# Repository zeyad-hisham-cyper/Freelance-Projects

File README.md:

# Freelance Projects

A portfolio of embedded systems, PCB design and IoT projects delivered for freelance clients and events, from schematic and PCB layout through firmware to companion mobile apps.

**Core skills:** ESP32 · Arduino / PlatformIO (C++) · KiCad 9 PCB design · sensor integration (IMU, IR temperature, load cells, PPG) · BLE · ESP-NOW · nRF24L01+ · Flutter · Li-Po power design

---

## Projects

| | Project | What it is | Hardware | Firmware / Software |
|---|---|---|:---:|:---:|
|  | **[Smart Posture Corrector](Smart-Posture-Corrector/)** | Two-board wearable with two IMUs that vibrates when you slouch and streams posture data to a Flutter app over BLE. | ✅ KiCad (2 boards) | ✅ ESP32 firmware + Flutter app |
|  | **[Digital Weighing Scale](Digital-Weighing-Scale/)** | Load-cell weighing indicator built in stages: research, ESP-NOW prototype, then a modular "one firmware, many scales" controller with a wireless remote display. | Research + BOM | ✅ Arduino / ESP32 firmware, Nextion HMI |
|  | **[Cow Health Monitor](Cow-Health-Monitor/)** | ESP32 carrier board plus two remote sensor boards for a livestock collar: body temperature, heart rate / SpO₂, motion and GPS. | ✅ KiCad (1- and 2-layer variants) | — |
|  | **[Smart Emergency Dispatch Sensor](Smart-Emergency-Dispatch-Sensor/)** | ESP32 board with an IR thermometer, a 6-axis IMU, a GPS header and a buzzer/LED alarm for heat, fire or impact events. | ✅ KiCad, 2-layer THT | — |
|  | **[Telecom Village SIM Adapter Badge](TelecomVillage-SIM-Adapter-Badge/)** | Credit-card-sized conference badge that doubles as a 2FF / 3FF / 4FF smart-card adapter, with ISO 7816 contacts broken out to test pads. | ✅ KiCad, SMT-assembly ready | — |

Each project folder has its own README with an overview, block diagram, BOM, pin mapping, PCB specifications, build instructions and a render gallery.

---

## Repository layout

```
Freelance-Projects/
├── Smart-Posture-Corrector/           # ESP32 firmware (PlatformIO) + Flutter app + KiCad PCBs
├── Digital-Weighing-Scale/            # Load-cell firmware (MVP + v2), Nextion HMI, research figures
├── Cow-Health-Monitor/                # KiCad PCB set + vendor 3D models
├── Smart-Emergency-Dispatch-Sensor/   # KiCad PCB + Gerbers
├── TelecomVillage-SIM-Adapter-Badge/  # KiCad PCB, Gerbers, pick-and-place, badge artwork
└── kicad-shared-lib/                  # Symbols, footprints and 3D models shared by several boards
```

Every hardware project follows the same pattern:

- **KiCad source:** `*.kicad_pro`, `*.kicad_sch`, `*.kicad_pcb`
- **Fabrication outputs:** Gerber and drill files, plus a zip ready to upload to JLCPCB / PCBWay
- **`docs/`:** 3D renders, PCB layout, schematic (SVG + PDF)

## Opening the KiCad projects

1. Install **KiCad 9.x**.
2. Clone the whole repository. Some boards load 3D models from `kicad-shared-lib/` or a sibling project through `${KIPRJMOD}`-relative paths, so the folder structure must stay intact.
3. Open the `.kicad_pro` file in the project folder.

## Regenerating the figures

The renders in each `docs/images/` folder were produced with `kicad-cli`:

```bash
kicad-cli pcb render --quality high --width 1600 --height 1000 --rotate " -45,0,35" -o docs/images/pcb_3d_iso.png board.kicad_pcb
kicad-cli pcb render --side top    --quality high -o docs/images/pcb_3d_top.png    board.kicad_pcb
kicad-cli pcb render --side bottom --quality high -o docs/images/pcb_3d_bottom.png board.kicad_pcb
kicad-cli pcb export svg --layers "F.Cu,B.Cu,Edge.Cuts,F.Silkscreen" --mode-single --page-size-mode 2 --exclude-drawing-sheet -o docs/images/pcb_layout.svg board.kicad_pcb
kicad-cli sch export svg -o docs/images/schematic board.kicad_sch
kicad-cli sch export pdf -o docs/schematic.pdf board.kicad_sch
```

## Third-party content

- Vendor symbols, footprints and 3D models (SnapEDA, DFRobot, CUI, GCT and others) remain under their owners' licences.
- The 3D-printable load-cell frame in `Digital-Weighing-Scale/` is © indrekluuk ([Thingiverse 4602226](https://www.thingiverse.com/thing:4602226)), licensed CC BY-NC.
- Event and university logos on the silkscreens belong to their respective owners.

---

**Author:** [@zeyad-hisham-cyper](https://github.com/zeyad-hisham-cyper) — Embedded Systems & PCB Design

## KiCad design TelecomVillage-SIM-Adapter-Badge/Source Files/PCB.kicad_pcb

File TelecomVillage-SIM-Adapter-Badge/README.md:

# Telecom Village Badge — Smart Card 2FF / 3FF / 4FF Adapter

> A credit-card-style conference badge PCB for **Telecom Village** (*"Malware Edition"*). It is also a working tool: three SIM-card sockets (Mini, Micro and Nano SIM) share one bus, and the ISO 7816 smart-card contacts are broken out to large test pads for probing.

| Front artwork | Back artwork |
|---|---|
|  |  |

---

## Overview

The board is a 2-layer, 1.6 mm FR-4 PCB. It is about **108 × 54 mm** with rounded corners, so it has the look of an event badge. The silkscreen on the copper side is **Telecom Village** artwork: a hooded hacker figure with a cell tower and a satellite dish, *"MALWARE EDITION"*, and the names of well-known telecom attacks and malware (SIMjacker, A5/1 cracker, GTPStorm, LightBasin, Skylock, Hermit spyware, VoLTEr attack). The silkscreen text names the board **"SMART CARD 2FF / 3FF / 4FF ADAPTER V1"**. The back carries a sponsor logo.

The design has no active parts. It has no MCU, regulator or firmware. Electrically it is a **passive SIM / UICC breakout**:

- **J2** is a 2FF (Mini SIM) socket, **J3** a 3FF (Micro SIM) socket and **J1** a 4FF (Nano SIM) socket. All three are wired in parallel to the same ISO 7816 nets.
- Eight **3.5 × 2 mm SMD test pads** (J4–J11) expose VCC, RST, CLK, I/O, VPP, GND and two spare AUX lines. You can connect them to a logic analyser, a smart-card reader, an SDR/SIM-tracing setup or a microcontroller.

*Inferred use:* hands-on SIM/UICC workshops at the village, such as sniffing APDUs, attaching a reader to a card of any size, or adapting one form factor to another. The design files don't state this. It follows from the topology and the event theme.

## Key features

- **Three SIM form factors on one badge:** 2FF / 3FF / 4FF sockets from CUI Devices and GCT.
- **All ISO 7816 contacts broken out:** C1 VCC, C2 RST, C3 CLK, C5 GND, C6 VPP and C7 I/O go to large SMD pads that are easy to clip or probe.
- **Two extra AUX pads** (AUX1/AUX2) for user wiring. They are not connected to the sockets.
- **GND pour on both layers** with about 240 stitching vias (0.6 mm / 0.3 mm drill).
- **Detailed silkscreen artwork** made from a custom ~430 kB KiCad footprint (`badge_fron`), plus a back-side sponsor logo.
- **Single-sided SMT assembly:** all 11 placed parts are on the top side.
- Gerbers, drill files, gerber job, pick-and-place and a STEP model are all included.

## Block diagram

```mermaid
flowchart LR
    subgraph Sockets["SIM sockets (in parallel)"]
        J2["J2 · 2FF Mini SIM<br/>GCT SIM7050-6-0-00-A"]
        J3["J3 · 3FF Micro SIM<br/>CUI MSIM-10-B"]
        J1["J1 · 4FF Nano SIM<br/>CUI NSIM-2-C"]
    end

    BUS(("ISO 7816 bus<br/>VCC · RST · CLK<br/>I/O · VPP · GND"))

    J2 --- BUS
    J3 --- BUS
    J1 --- BUS

    subgraph Pads["Test pads (3.5 × 2 mm SMD)"]
        P1["J4 VCC"]
        P2["J5 RST"]
        P3["J6 CLK"]
        P4["J10 AUX1"]
        P5["J7 GND"]
        P6["J8 VPP"]
        P7["J9 I/O"]
        P8["J11 AUX2"]
    end

    BUS --- P1 & P2 & P3 & P5 & P6 & P7
    EXT["External reader / logic analyser /<br/>MCU / SIM tracer (user-supplied)"] -.-> Pads
```

## Bill of materials

Taken from the schematic and `Fabrication Files/PCB-top.pos`.

| Ref | Qty | Value / MPN | Manufacturer | Description | Footprint |
|---|---|---|---|---|---|
| J1 | 1 | NSIM-2-C | CUI Devices | Nano SIM (4FF) connector, 6 pos, hinged, SMT, 1.4 mm height | `Library:NSIM2C` |
| J2 | 1 | SIM7050-6-0-00-A | GCT | Mini SIM (2FF) connector, 6 pos, SMT | `Library:SIM70506000A` |
| J3 | 1 | MSIM-10-B | CUI Devices | Micro SIM (3FF) connector, 6 pos, push-in/pull-out, SMT, 1.8 mm height | `Library:MSIM10B` |
| J4–J11 | 8 | Conn_01x01 | — | Bare copper SMD test pad, 3.5 × 2 mm (no part to place) | `Library:PAD` |
| G\*\*\* | 2 | — | — | Silkscreen artwork: front badge art and back sponsor logo | `Library:badge_fron`, `Library:pcbway_logo` |

Datasheet links are stored in `Source Files/Library.kicad_sym`.

> Only **3 real components** need to be bought (J1–J3). J4–J11 are copper pads that appear in the CPL file. Remove them from the placement file before ordering assembly.

## Pin mapping (ISO 7816 contacts)

The board has no MCU. The table shows how each socket contact and test pad maps to a net.

| Net | Socket pad (J1 / J2 / J3) | Test pad | ISO 7816 function |
|---|---|---|---|
| VCC | C1 | J4 | Card supply |
| RST | C2 | J5 | Reset |
| CLK | C3 | J6 | Clock |
| GND | C5 + shield/mounting pads MP1–MP4 | J7 | Ground |
| VPP | C6 | J8 | Programming voltage / SWP (on modern UICCs) |
| I/O | C7 | J9 | Half-duplex serial data |
| AUX1 | — | J10 | Spare pad (net label only) |
| AUX2 | — | J11 | Spare pad (net label only) |

The pads sit in two columns of four on the left side of the badge. J4–J6 and J10 (x = 173.9 mm) form one column, and J7–J9 and J11 (x = 182.8 mm) form the other, at a 2.5 mm pitch.

## Power

The board has no on-board power. Whatever device is connected to the **VCC (J4) / GND (J7)** pads supplies the inserted SIM. ISO 7816 / 3GPP cards normally run at class C/B/A, which is 1.8 V, 3 V or 5 V. There is no regulation, protection or level shifting, so the user must match the card's voltage class. *(This is a general ISO 7816 note, not something stated in the design files.)*

> ⚠️ All three sockets share one bus. Insert **only one SIM at a time**.

## PCB specifications

| Parameter | Value |
|---|---|
| EDA tool | KiCad 8.0 (files generated with 8.0.6) |
| Layers | 2 (F.Cu / B.Cu) |
| Board outline | 107.95 × 53.975 mm, 2.54 mm corner radius (job file reports 108.05 × 54.075 mm including the outline stroke) |
| Thickness | 1.6 mm FR-4, 35 µm copper |
| Min. track / clearance | 0.4 mm track (from the job file); 0.2 mm pad/track clearance |
| Track widths used | 0.2 / 0.4 / 0.6 mm |
| Vias | 255 × 0.6 mm pad / 0.3 mm drill (mostly GND stitching) |
| Copper pours | GND zone on both layers |
| Plated holes / NPTH | Vias only. The NPTH file is empty, and the outline has no lanyard hole (see Notes) |
| Surface finish | Not specified (job file: `None`) |
| Silkscreen | Front: Telecom Village artwork, attack names, board title. Back: sponsor logo |

## Assembly

| Side | Placements in `.pos` | Real parts |
|---|---|---|
| Top | 11 (J1–J11) | 3 SIM sockets |
| Bottom | 0 | — |

- **Single-sided SMT.** The board needs no through-hole parts and only one reflow pass.
- `PCB-top.pos` / `PCB-bottom.pos` are KiCad CSV-style placement files in mm, using absolute board coordinates. For JLCPCB/PCBWay assembly, rename the columns to `Designator, Mid X, Mid Y, Layer, Rotation` and remove J4–J11. Check the socket rotations against the fab's preview.
- No BOM CSV is included. The table above contains everything needed to make one.

## Gallery

| Isometric | Top | Bottom |
|---|---|---|
|  |  |  |

**PCB layout:** 

**Schematic:** 

A PDF of the schematic is in [`docs/schematic.pdf`](docs/schematic.pdf).

## Repository structure

```
TelecomVillage-SIM-Adapter-Badge/
├── README.md
├── Badge Design_FRONT.png        # front artwork (source for silkscreen)
├── Badge Design_BACK.png         # back artwork
├── 3D File/
│   └── PCB.step                  # full-board 3D model
├── Fabrication Files/
│   ├── PCB-*.gbr                 # Cu, mask, paste, silk, edge cuts, drill maps
│   ├── PCB-PTH.drl / PCB-NPTH.drl
│   ├── PCB-job.gbrjob
│   ├── PCB-top.pos / PCB-bottom.pos
│   └── gerber.zip                # same gerbers + drills, zipped for upload
├── Source Files/
│   ├── PCB.kicad_pro / .kicad_sch / .kicad_pcb
│   ├── Library.kicad_sym         # custom symbols (3 SIM sockets)
│   ├── Library.pretty/           # custom footprints (sockets, PAD, artwork logos)
│   ├── 3D/                       # STEP models of the SIM sockets
│   └── fp-lib-table / sym-lib-table
└── docs/
    ├── schematic.pdf
    └── images/                   # 3D renders, layout & schematic SVGs
```

## How to open / manufacture

1. **Open:** install KiCad 8 or newer (KiCad 9 opens and upgrades the files). Open `Source Files/PCB.kicad_pro`. The project-local tables (`fp-lib-table`, `sym-lib-table`) load the custom `Library`, and the 3D models resolve through `${KIPRJMOD}/3D`.
2. **Order bare PCBs:** upload `Fabrication Files/gerber.zip` to JLCPCB, PCBWay or a similar fab. Use 2 layers, 1.6 mm thickness and a finish of your choice. For a badge, a black or white mask with the opposite silkscreen colour is recommended.
3. **Assembly (optional):** order J1–J3 using the BOM table, and use `PCB-top.pos` as the CPL (see Assembly). The sockets can also be hand-soldered with hot air or a fine-tip iron.
4. **Use:** insert one SIM, then connect your reader or analyser to the VCC/GND/CLK/RST/I/O pads.

## Notes

- The **lanyard slot** in the artwork is drawn on silkscreen only. The `Edge.Cuts` outline is a plain rounded rectangle, so attaching a lanyard would need a clip or an extra slot in a future revision.
- The drill files (`PCB-PTH.drl`) were generated on 2024-07-02, and the gerbers were regenerated on 2025-05-31 after artwork changes. Re-export the drills together with the gerbers before ordering.
- The 3D model linked to the MSIM-10-B footprint is `693010020611 (rev1).stp` (appears to be a Würth part number), and the one for NSIM-2-C is `G85D1160022HHR`. These look like stand-in models, so check the renders against the actual parts.

---

**Author:** [@zeyad-hisham-cyper](https://github.com/zeyad-hisham-cyper) — Embedded Systems & PCB Design · Part of the [Freelance Projects](../README.md) portfolio

*"Telecom Village" artwork and the sponsor logo belong to their respective owners and are shown here as portfolio context only.*

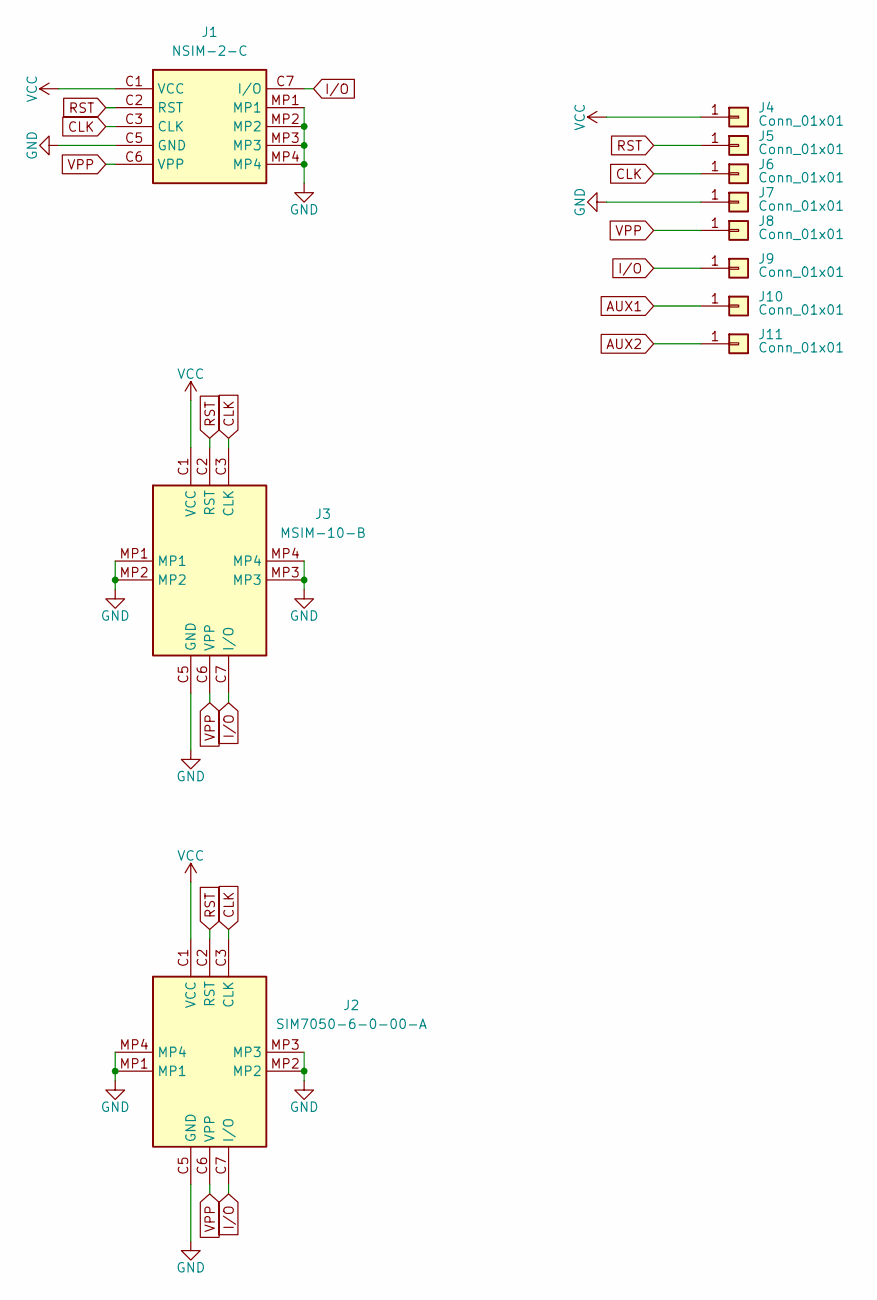
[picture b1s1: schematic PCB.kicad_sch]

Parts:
J1: NSIM-2-C; NSIM2C; Manufacturer_Part_Number NSIM-2-C; Mouser Part Number 179-NSIM-2-C
J2: SIM7050-6-0-00-A; SIM70506000A; Manufacturer_Part_Number SIM7050-6-0-00-A; Mouser Part Number 640-SIM7050-6-0-00-A
J3: MSIM-10-B; MSIM10B; Manufacturer_Part_Number MSIM-10-B; Mouser Part Number 179-MSIM-10-B
J4, J5, J6, J7, J8, J9, J10, J11: Conn_01x01; PAD

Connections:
AUX1: J10.1
AUX2: J11.1
CLK: J1.C3 (CLK), J2.C3 (CLK), J3.C3 (CLK), J6.1
GND: J1.C5 (GND), J1.MP1, J1.MP2, J1.MP3, J1.MP4, J2.C5 (GND), J2.MP1, J2.MP2, J2.MP3, J2.MP4, J3.C5 (GND), J3.MP1, J3.MP2, J3.MP3, J3.MP4, J7.1
I/O: J1.C7 (I/O), J2.C7 (I/O), J3.C7 (I/O), J9.1
RST: J1.C2 (RST), J2.C2 (RST), J3.C2 (RST), J5.1
VCC: J1.C1 (VCC), J2.C1 (VCC), J3.C1 (VCC), J4.1
VPP: J1.C6 (VPP), J2.C6 (VPP), J3.C6 (VPP), J8.1

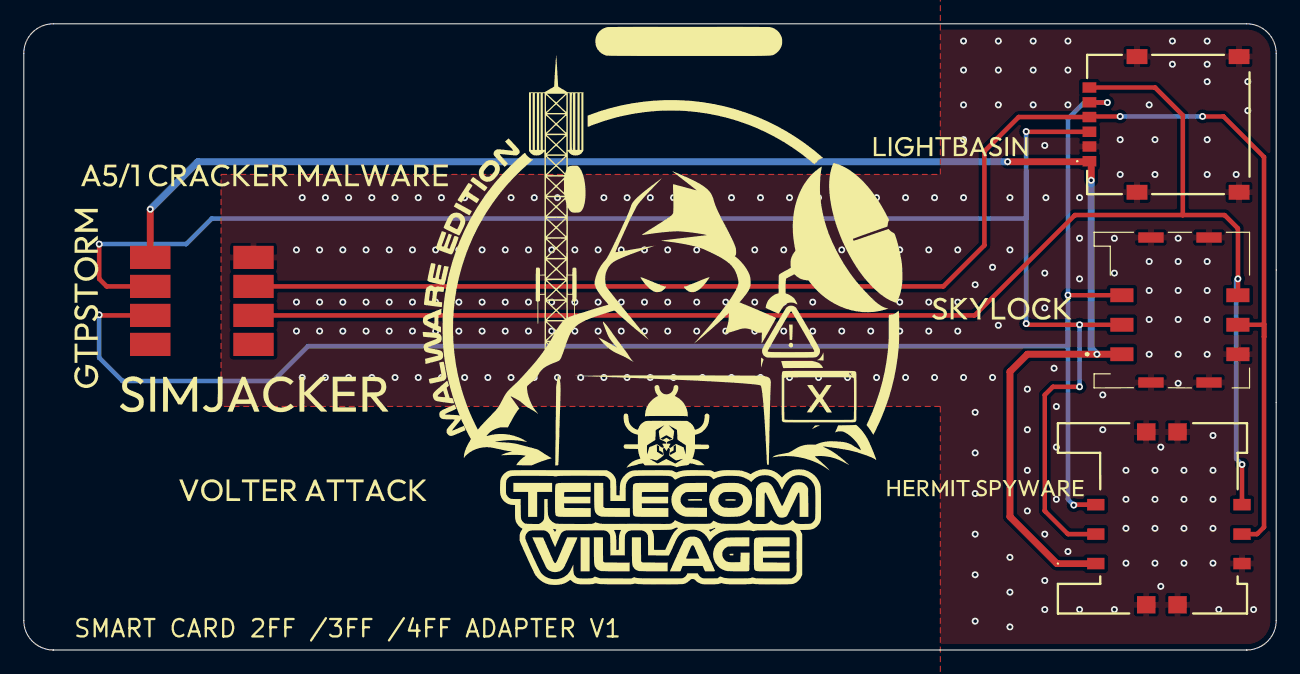
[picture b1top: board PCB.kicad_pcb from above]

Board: 2 copper layers, 107.9 x 54.0 mm, 11 parts (0 on the bottom side), 6 nets.

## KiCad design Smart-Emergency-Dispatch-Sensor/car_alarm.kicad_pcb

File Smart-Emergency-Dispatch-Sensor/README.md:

# Smart Emergency Dispatch Sensor (V1.0)

**An ESP32-based sensor board that pairs an IR thermometer with a 6-axis motion sensor and a GPS header, built to detect heat, fire or impact events and raise a local alarm.** Designed in KiCad 9 as a 2-layer, 100 × 60 mm through-hole PCB.

---

## Overview

The *Smart Emergency Dispatch Sensor* is a carrier PCB for an **ESP32-DevKitC-32E** module. It brings together:

- an **MLX90614** non-contact infrared temperature sensor, for heat and fire detection,
- a **GY-521 (MPU-6050)** accelerometer/gyroscope breakout, for motion, tilt or impact detection (inferred from the "MPU Sensor" block),
- a **4-pin UART header** marked *"GPS Connector"* in the schematic, for an external GPS module,
- a **buzzer** and two indicator LEDs, silkscreened **Fire** and **Heat**,
- a **DC barrel-jack input**, with a power slide switch and an LM7805 5 V regulator.

The project folder is named `car_alarm`, and the sensor mix of temperature, motion and GPS points to a **vehicle emergency or crash-and-fire alert unit** that can report its location over the ESP32's Wi-Fi/Bluetooth. That purpose is *inferred* from the hardware: the repository holds the hardware design only.

The board is silkscreened *"Smart Emergency Dispatch Sensor — V 1.0 — 2026"* and carries the Misr International University (MIU) 30th-anniversary logo.

## Key features

- **ESP32-DevKitC-32E** socketed as a module: Wi-Fi + BLE, and USB programming through the DevKit's own USB port
- **Shared I²C bus** (GPIO21 = SDA, GPIO22 = SCL) for the MLX90614 IR thermometer and the MPU-6050 IMU
- **UART header (J1)** on the ESP32's UART0 (TXD0/RXD0) with a 3.3 V supply, for a GPS module
- **Local alarm outputs**: a 12 mm buzzer and two 5 mm LEDs (Fire / Heat) with 220 Ω current limiting
- **Power input**: a horizontal DC barrel jack → slide on/off switch → LM7805 (TO-220) → 5 V into the DevKit; the DevKit's onboard LDO then supplies the 3.3 V rail for the sensors
- **Through-hole design** for easy hand assembly: every part is THT, and the ESP32 and GY-521 are plug-in modules
- **Solid GND pour** on the bottom layer, with a copper keep-out under the ESP32 antenna area
- **Production files included**: Gerber + Excellon drill + job file, exported from KiCad 9.0.2

## Block diagram

```mermaid
flowchart LR
    DC["DC barrel jack<br/>J9"] --> SW["Slide switch<br/>SW1"]
    SW --> REG["LM7805<br/>U6 (C3 / C4)"]
    REG -- "+5 V → EXT_5V" --> ESP["ESP32-DevKitC-32E<br/>U3"]
    ESP -- "+3.3 V (DevKit LDO)" --> RAIL["3.3 V rail<br/>C1, C2, C5"]

    RAIL --> IR["MLX90614 IR temp<br/>U2"]
    RAIL --> IMU["GY-521 / MPU-6050<br/>U1"]
    RAIL --> GPS["GPS header<br/>J1"]

    ESP <-- "I²C: SDA IO21 / SCL IO22" --> IR
    ESP <-- "I²C: SDA IO21 / SCL IO22" --> IMU
    ESP <-- "UART0: TXD0 / RXD0" --> GPS

    ESP -- "IO32" --> BZ["Buzzer<br/>BZ1"]
    ESP -- "IO26 → R7" --> FIRE["Fire LED<br/>D6"]
    ESP -- "IO27 → R6" --> HEAT["Heat LED<br/>D5"]
```

## Schematic

The design fits on one sheet, split into labelled blocks: *Input and 5V Circuit*, *ESP-32*, *TEMP Sensor*, *MPU Sensor*, *Indicator* and *GPS Connector*. A PDF copy is at [`docs/schematic.pdf`](docs/schematic.pdf).

## Bill of materials

| Ref | Value | Footprint | Qty | Purpose |
|---|---|---|---|---|
| U3 | ESP32-DevKitC-32E | `ESP32-DEVKITC-32E:MODULE_ESP32-DEVKITC-32E` | 1 | Main MCU module (Wi-Fi/BLE) |
| U2 | MLX90614ESF-BAA-000-TU | `TO254P942H425-4` (TO-39, 4-pin) | 1 | Non-contact IR temperature sensor (3 V version), I²C |
| U1 | GY-521 | `GY-521:GY-521` | 1 | MPU-6050 accelerometer + gyroscope breakout, I²C |
| U6 | LM7805_TO220 | `Package_TO_SOT_THT:TO-220-3_Vertical` | 1 | 5 V linear regulator |
| J9 | Barrel_Jack_Switch | `Connector_BarrelJack:BarrelJack_Horizontal` | 1 | DC power input |
| SW1 | Slide switch (Würth 450301014042 symbol) | `SW_Slide-03_Wuerth-WS-SLTV_10x2.5x6.4_P2.54mm` | 1 | Power on/off |
| J1 | Conn_01x04 | `PinSocket_1x04_P2.54mm_Horizontal` | 1 | GPS / UART header (3.3V, TX, RX, GND) |
| BZ1 | Buzzer | `Buzzer_Beeper:Buzzer_12x9.5RM7.6` | 1 | Audible alarm |
| D6 | LED (Fire) | `LED_THT:LED_D5.0mm` | 1 | Fire indicator |
| D5 | LED (Heat) | `LED_THT:LED_D5.0mm` | 1 | Heat indicator |
| R6, R7 | 220 Ω | `R_Axial_DIN0207_L6.3mm_D2.5mm_P7.62mm_Horizontal` | 2 | LED current limiting |
| C3 | 0.33 µF | `C_Radial_D5.0mm_H5.0mm_P2.00mm` | 1 | LM7805 input capacitor |
| C4 | 0.1 µF | `C_Radial_D5.0mm_H5.0mm_P2.00mm` | 1 | LM7805 output capacitor (5 V) |
| C2 | 100 µF | `C_Radial_D5.0mm_H5.0mm_P2.00mm` | 1 | 3.3 V bulk capacitor |
| C1, C5 | 0.1 µF | `C_Radial_D5.0mm_H5.0mm_P2.00mm` | 2 | 3.3 V decoupling (C5 is placed next to the MLX90614) |

**Total:** 17 placed components, all through-hole.

## ESP32 pin mapping

| ESP32 pin | Net | Connected to | Function |
|---|---|---|---|
| IO21 | `SDA` | U2 pin 2 (SDA/PWM), U1 SDA | I²C data |
| IO22 | `SCL` | U2 pin 1 (SCL/Vz), U1 SCL | I²C clock |
| TXD0 | `TX` | J1 pin 2 | UART0 TX → GPS |
| RXD0 | `RX` | J1 pin 3 | UART0 RX ← GPS |
| IO32 | `buzzer` | BZ1 (+) | Buzzer drive (direct from the GPIO) |
| IO26 | `LED1` | R7 → D6 (Fire) | Fire LED |
| IO27 | `LED2` | R6 → D5 (Heat) | Heat LED |
| EXT_5V | `5V` | LM7805 output | 5 V supply into the DevKit |
| 3V3 | `+3.3V` | U1, U2, J1, C1/C2/C5 | 3.3 V supply out of the DevKit |
| GND (×3) | `GND` | Ground pour | Ground |

All other ESP32 pins are left unconnected. That leaves GPIO4, 5, 13–19, 23, 25, 33–35 and others free for future expansion. The GY-521's `INT`, `AD0`, `XDA` and `XCL` pins are not connected, so the MPU-6050 sits at its default I²C address (0x68). The MLX90614 defaults to 0x5A, so the two sensors share the bus without conflict.

## Power design

```
DC jack (J9) ──► SW1 (on/off) ──► LM7805 (U6) ──► +5V ──► ESP32 DevKit EXT_5V
                                   C3 0.33µF in        │
                                   C4 0.1µF out        ▼
                                              DevKit onboard 3.3 V LDO
                                                       │
                                     +3.3V ──► MLX90614, GY-521, J1 (GPS)
                                               C1 0.1µF, C5 0.1µF, C2 100µF
```

- The input capacitors (0.33 µF in, 0.1 µF out) follow the standard LM7805 datasheet circuit.
- No separate 3.3 V regulator is fitted: the 3.3 V rail comes from the ESP32-DevKitC's own LDO through its `3V3` pin.
- The input voltage is not stated in the files. The LM7805 needs about 7 V or more at its input, so a 9–12 V adapter (or a 12 V vehicle supply, inferred) is the intended source.

## PCB specifications

| Parameter | Value |
|---|---|
| Board size | 100 × 60 mm (rectangular outline) |
| Layers | 2 (F.Cu / B.Cu) |
| Thickness | 1.6 mm |
| Track width | 0.6 mm on every track (79 segments, mostly routed on B.Cu) |
| Clearance (net class) | 0.5 mm |
| Minimum clearance (board rule) | 0.4 mm |
| Copper-to-edge clearance | 0.8 mm |
| Vias | 6, 1.4 mm pad / 0.6 mm drill |
| Drill sizes (PTH) | 0.6 – 1.1 mm |
| NPTH | 2 × 3.0 mm (GY-521 mounting holes) |
| Copper pour | GND zone on B.Cu |
| Keep-out | B.Cu copper/track/via keep-out under the ESP32 antenna area |
| Surface finish | Not specified (choose at the fab, e.g. HASL) |
| Components | 100 % through-hole, all on the top side |
| EDA | KiCad 9.0 |

The track and clearance rules are wide (0.6 mm tracks, 0.4–0.5 mm clearances), so the board fits the cheapest standard fab tiers and could also be home-etched or milled.

## Gallery

| Top | Bottom |
|---|---|
|  |  |

**PCB layout**

## Repository structure

```
Smart-Emergency-Dispatch-Sensor/
├── car_alarm.kicad_pro        # KiCad project
├── car_alarm.kicad_sch        # Schematic (single sheet)
├── car_alarm.kicad_pcb        # PCB layout
├── gerber/                    # Gerbers + Excellon drill + job file (KiCad 9.0.2)
├── gerber.zip                 # Same fabrication files, zipped for upload
├── lib/
│   └── MLX90614ESF-BAA-000-TU/  # Symbol, footprint and STEP model (SnapEDA)
└── docs/
    ├── schematic.pdf
    └── images/                # 3D renders, layout and schematic SVGs
```

## How to open and manufacture

1. **Open** `car_alarm.kicad_pro` in **KiCad 9** or later.
2. **Order PCBs**: upload `gerber.zip` as-is to **JLCPCB**, **PCBWay** or any similar fab. The job file says 2 layers, 1.6 mm thick, 100 × 60 mm. Standard options (FR-4, HASL, any solder-mask colour) are fine.
3. **Assemble**: every part is through-hole. Solder the passives, LEDs, buzzer and connectors first, then the regulator. Use female headers for the ESP32-DevKitC and the GY-521 so both can be removed.

> **Library note:** the MLX90614 library lives in `lib/`. The ESP32-DevKitC-32E and GY-521 symbols and footprints, and some 3D models, point to library paths outside this folder. The board files still open, and the Gerbers are complete, but a few 3D models may be missing in the 3D viewer.

## Status and next steps

- ✅ Schematic, PCB layout and fabrication outputs are complete (V1.0).
- ⏳ **No firmware is included.** It still needs: I²C drivers for the MLX90614 and MPU-6050, threshold or impact detection, GPS NMEA parsing, buzzer/LED alerts, and a Wi-Fi/BLE dispatch path.
- Possible hardware improvements for a V1.1:
  - add a transistor driver for the buzzer (it currently runs straight from GPIO32),
  - move the GPS from UART0 to UART2 so it doesn't clash with the USB programming/console port,
  - add board mounting holes,
  - add reverse-polarity protection on the DC input.

---

**Author:** [@zeyad-hisham-cyper](https://github.com/zeyad-hisham-cyper) — Embedded Systems & PCB Design · Part of the [Freelance Projects](../README.md) portfolio

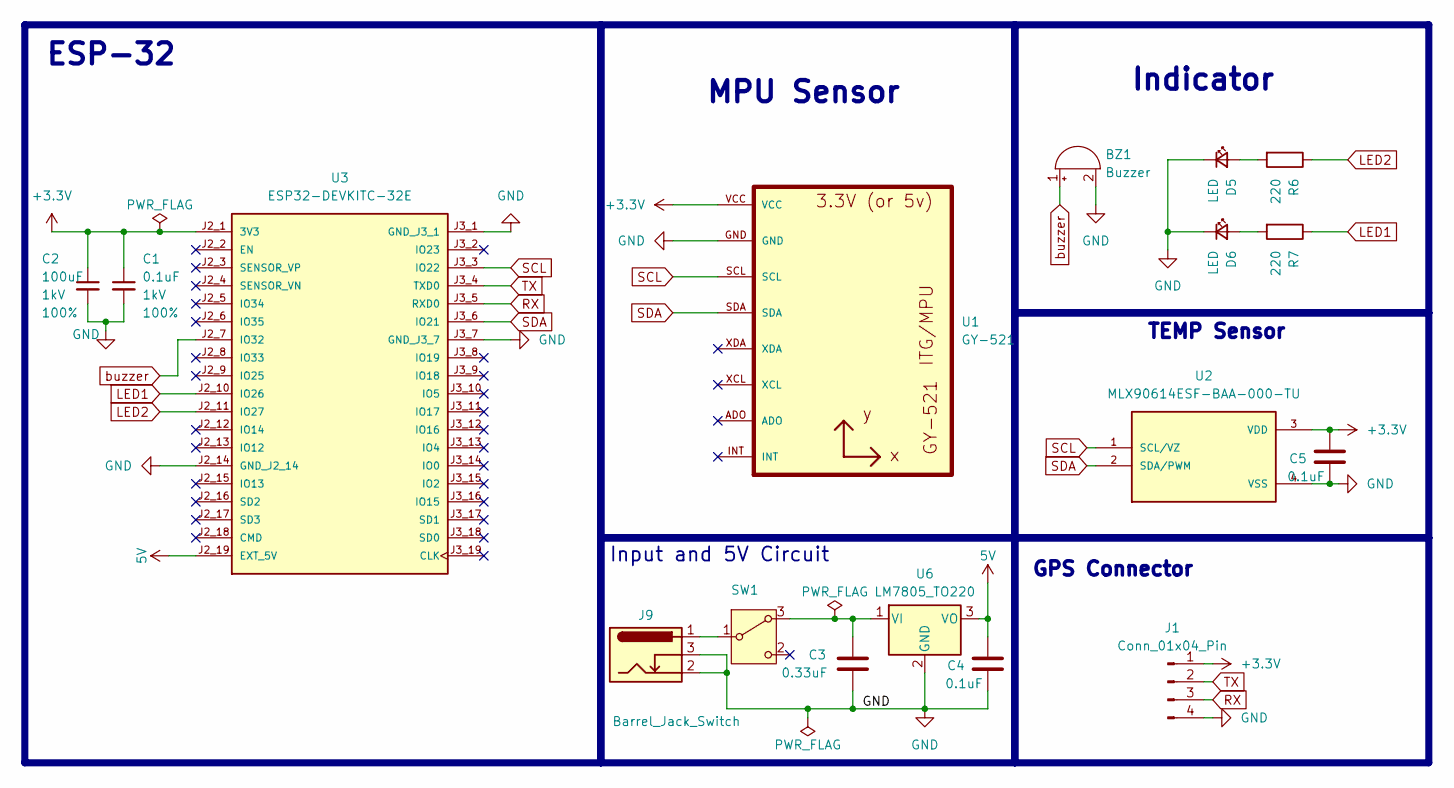
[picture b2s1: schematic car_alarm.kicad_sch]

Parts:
BZ1: Buzzer; Buzzer_12x9.5RM7.6
C1: 0.1uF; C_Radial_D5.0mm_H5.0mm_P2.00mm; Voltage 1kV; Tolerance 100%
C2: 100uF; C_Radial_D5.0mm_H5.0mm_P2.00mm; Voltage 1kV; Tolerance 100%
C3: 0.33uF; C_Radial_D5.0mm_H5.0mm_P2.00mm
C4, C5: 0.1uF; C_Radial_D5.0mm_H5.0mm_P2.00mm
D5, D6: LED; LED_D5.0mm
J1: Conn_01x04_Pin; PinSocket_1x04_P2.54mm_Horizontal
J9: Barrel_Jack_Switch; BarrelJack_Horizontal
R6, R7: 220; R_Axial_DIN0207_L6.3mm_D2.5mm_P7.62mm_Horizontal
SW1: SW_Wuerth_450301014042; SW_Slide-03_Wuerth-WS-SLTV_10x2.5x6.4_P2.54mm
U1: GY-521
U2: MLX90614ESF-BAA-000-TU; TO254P942H425-4; PARTREV 13
U3: ESP32-DEVKITC-32E; MODULE_ESP32-DEVKITC-32E; PARTREV 1.4
U6: LM7805_TO220; TO-220-3_Vertical

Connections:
5V: C4.1, U3.J2_19 (EXT_5V), U6.3 (VO)
+3.3V: C1.1, C2.1, C5.1, J1.1, U1.VCC, U2.3 (VDD), U3.J2_1 (3V3)
GND: BZ1.2 (-), C1.2, C2.2, C3.2, C4.2, C5.2, D5.1 (K), D6.1 (K), J1.4, J9.2, J9.3, U1.GND, U2.4 (VSS), U3.J2_14 (GND_J2_14), U3.J3_1 (GND_J3_1), U3.J3_7 (GND_J3_7), U6.2 (GND)
LED1: R7.1, U3.J2_10 (IO26)
LED2: R6.1, U3.J2_11 (IO27)
unnamed: D5.2 (A), R6.2
unnamed: D6.2 (A), R7.2
unnamed: C3.1, SW1.3 (A), U6.1 (VI)
unnamed: J9.1, SW1.1 (B)
RX: J1.3, U3.J3_5 (RXD0)
SCL: U1.SCL, U2.1 (SCL/VZ), U3.J3_3 (IO22)
SDA: U1.SDA, U2.2 (SDA/PWM), U3.J3_6 (IO21)
TX: J1.2, U3.J3_4 (TXD0)
buzzer: BZ1.1 (+), U3.J2_7 (IO32)

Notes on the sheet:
GPS Connector
Indicator
TEMP Sensor
ESP-32
Input and 5V Circuit
MPU Sensor

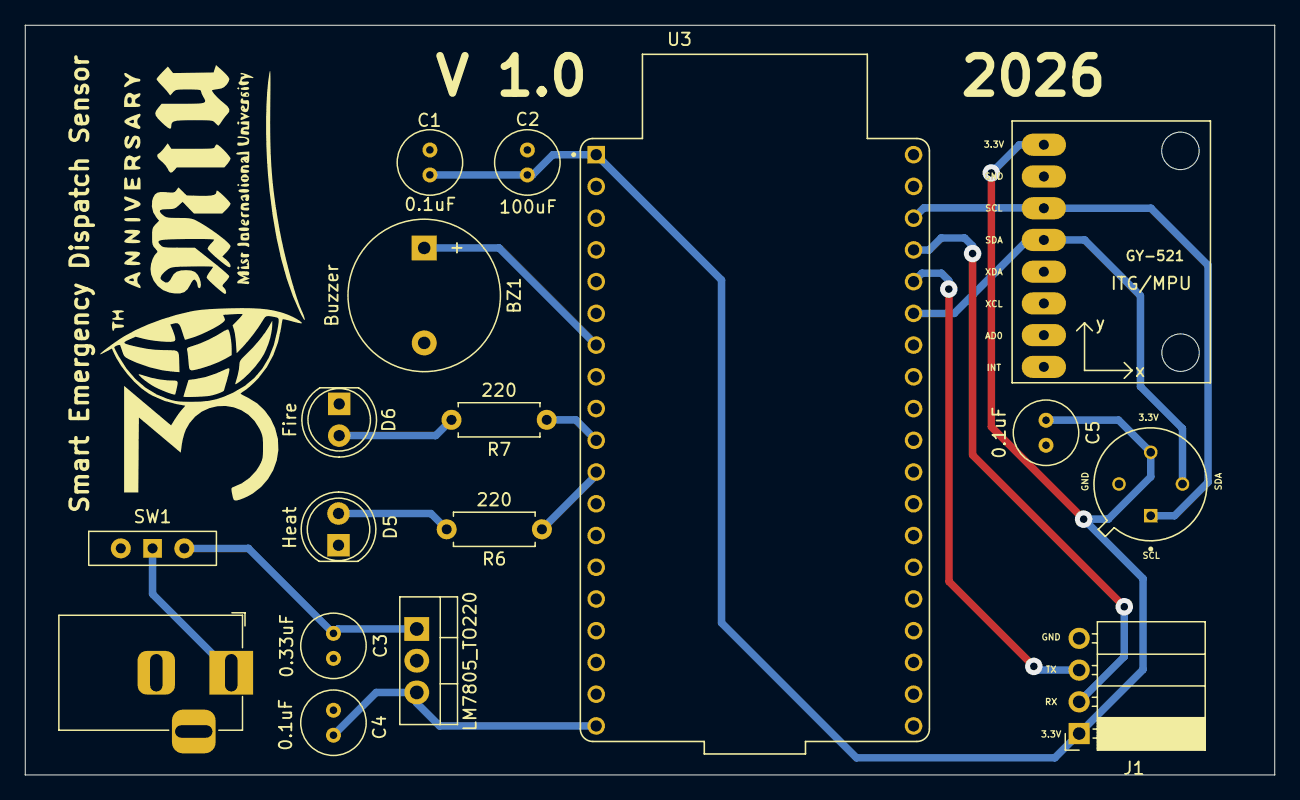
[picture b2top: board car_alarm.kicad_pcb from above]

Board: 2 copper layers, 100.0 x 60.0 mm, 17 parts (0 on the bottom side), 14 nets.

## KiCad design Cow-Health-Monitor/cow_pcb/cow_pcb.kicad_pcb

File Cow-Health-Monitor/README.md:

# Cow Health-Monitoring Collar: ESP32 Sensor PCB

**An ESP32 carrier board and two small sensor boards for a wearable that monitors a cow's vital signs. It brings together body temperature, heart rate / SpO₂, motion and GPS on one powered PCB set, designed in KiCad 9.**

---

## Overview

This is the hardware for a livestock health monitor. A carrier board holds an **ESP32-DevKitC-32E** and connects it to:

- a **non-contact IR thermometer** (GY-906 module, MLX90614-class) for body/skin temperature
- **pulse-oximeter / heart-rate modules** (DFRobot **SEN0344**, MAX30102-based)
- a **10-DOF motion module** (GY-87: accelerometer/gyro/magnetometer/barometer) for activity and posture
- a **GPS module** header for location tracking

The design is split into **three boards in one KiCad file**: the main carrier board and two small remote sensor boards. These connect to the main board over 4-pin JST-XH I²C cables, so the temperature and pulse sensors can sit against the animal's skin away from the electronics. *(The cable pairing is inferred from the matching connector pin-outs. See [Connectors](#connectors-and-inter-board-wiring).)*

> Scope: this repository contains **hardware only**: schematic, PCB layout, Gerbers and 3D models. There is no firmware in this folder.

## Key features

- **ESP32-DevKitC-32E** plugs straight in, giving Wi-Fi + BLE and USB programming with no RF or USB-UART design needed on the carrier
- **Shared I²C bus** (GPIO21/22) for the IMU, IR thermometer and remote pulse sensor
- **Second pulse-sensor footprint on UART2** (GPIO16/17), so the DFRobot SEN0344 can run in its UART mode
- **GPS header on UART0** with two 2-pin jumper headers ("UART CAP"), so the GPS can be disconnected from the ESP32's USB-programming UART *(purpose inferred)*
- **Barrel-jack input → slide ON/OFF switch → LM7805 regulator**, with a marked heatsink area on the silkscreen
- **Copper keep-out under the ESP32 antenna** and a **GND pour on the bottom layer** of all three boards
- Only **through-hole parts and plug-in modules**, so it is easy to hand-solder and prototype
- **Two fabrication outputs**: a full **2-layer** Gerber set and a **1-layer** (bottom copper only) set for single-sided or home etching

## Block diagram

```mermaid
flowchart LR
    DC["DC barrel jack<br/>J9"] --> SW["Slide switch<br/>SW1 (ON/OFF)"]
    SW --> REG["LM7805<br/>U6 → 5 V"]
    REG -- "5V → EXT_5V" --> ESP["ESP32-DevKitC-32E<br/>U3"]
    ESP -- "3V3 out → +3.3V rail" --> RAIL(("+3.3 V"))

    subgraph MAIN["Main board"]
        ESP
        IMU["GY-87 10-DOF IMU<br/>U2"]
        HR1["SEN0344 MAX30102<br/>U4 (UART)"]
        GPS["GPS header<br/>J1"]
        JMP["UART jumpers<br/>J3 / J4"]
    end

    subgraph HRB["Pulse-sensor board"]
        HR2["SEN0344 MAX30102<br/>U5 (I²C)"]
    end

    subgraph TB["Temperature board"]
        IR["GY-906 IR thermometer<br/>U1"]
    end

    ESP <-- "I²C: SDA GPIO21 / SCL GPIO22" --> IMU
    ESP <-- "I²C via J6 ↔ J5<br/>(2 kΩ R1/R2)" --> HR2
    ESP <-- "I²C via J7 ↔ J8" --> IR
    ESP <-- "UART2: GPIO16 / GPIO17" --> HR1
    ESP <-- "UART0: TXD0 / RXD0" --> JMP <--> GPS
```

## Bill of materials

Generated from the schematic (`cow_pcb.kicad_sch`).

| Ref | Qty | Value / Part | Footprint | Function |
|---|---|---|---|---|
| U3 | 1 | ESP32-DEVKITC-32E | `ESP32-DEVKITC-32E:MODULE_ESP32-DEVKITC-32E` | Main MCU (Wi-Fi/BLE dev board) |
| U2 | 1 | GY-87 | `GY-87:GY-87` | 10-DOF IMU module (I²C) |
| U1 | 1 | GY-906 | `GY-609:Untitled` | IR thermometer module (I²C) |
| U4, U5 | 2 | DFRobot SEN0344 | `SEN0344:SEN0344` | MAX30102 heart-rate / SpO₂ (U4 on UART, U5 on I²C) |
| U6 | 1 | LM7805_TO220 | `TO-220-3_Vertical` | 5 V linear regulator |
| C3 | 1 | 0.33 µF | `C_Radial_D5.0mm` | Regulator input capacitor |
| C4 | 1 | 0.1 µF | `C_Radial_D5.0mm` | Regulator output capacitor (5 V) |
| C1 | 1 | 0.1 µF | `C_Radial_D5.0mm` | 3.3 V decoupling |
| C2 | 1 | 100 µF | `C_Radial_D5.0mm` | 3.3 V bulk capacitor |
| R1, R2 | 2 | 2 kΩ | `R_Axial_DIN0207_L6.3mm` | In series with SDA/SCL on the remote SEN0344 (U5) |
| J9 | 1 | Barrel_Jack_Switch | `BarrelJack_Horizontal` | DC power input |
| SW1 | 1 | Slide switch (Würth 450301014042 symbol) | `SW_Slide-03_Wuerth-WS-SLTV_10x2.5x6.4_P2.54mm` | Power ON/OFF |
| J1 | 1 | Conn_01x04 | `PinSocket_1x04_P2.54mm_Horizontal` | GPS module header (3V3, RX, TX, GND) |
| J3, J4 | 2 | Conn_01x02 | `PinHeader_1x02_P2.54mm_Vertical` | UART0 ↔ GPS jumpers |
| J5–J8 | 4 | 4-pin JST | `JST_XH_B4B-XH-A_1x04_P2.50mm_Vertical` | I²C + power links between the boards |

> The connector symbol value says "JST_1mm_4", but the footprint actually assigned is **JST-XH 2.50 mm**. The footprint is what gets built.

## ESP32 pin mapping

DevKitC-32E header pins as named in the schematic symbol (`J2_x` / `J3_x` = header/pin).

| ESP32 pin | Header pin | Net | Connected to |
|---|---|---|---|
| GPIO21 | J3_6 | `SDA` | U2 GY-87, U1 GY-906 (via J7/J8), U5 SEN0344 (via J6/J5 + R1) |
| GPIO22 | J3_3 | `SCL` | U2 GY-87, U1 GY-906 (via J7/J8), U5 SEN0344 (via J6/J5 + R2) |
| GPIO16 (UART2 RX) | J3_12 | `DF_TX` | U4 SEN0344 **TX** |
| GPIO17 (UART2 TX) | J3_11 | `DF_RX` | U4 SEN0344 **RX** |
| TXD0 (GPIO1) | J3_4 | `MCU_TX` | J4 pin 1 → (jumper) → `SEN_RX` → J1 pin 2 (GPS RX) |
| RXD0 (GPIO3) | J3_5 | `MCU_RX` | J3 pin 1 → (jumper) → `SEN_TX` → J1 pin 3 (GPS TX) |
| EXT_5V | J2_19 | `5V` | LM7805 output |
| 3V3 | J2_1 | `+3.3V` | Supply rail for every sensor and connector |
| GND | J2_14, J3_1 | `GND` | Common ground |

All other GPIOs are unconnected, which leaves room for later expansion. Interrupt and reset pins (MAX30102 `INT`/`RST`, GY-87 `INTA`/`DRDY`/`FSYNC`) are also left unconnected. A hand-written DevKit header map used during layout is in [`lib/esp32 pinout.txt`](lib/esp32%20pinout.txt).

### Connectors and inter-board wiring

| Connector | Board | Pin 1 → 4 |
|---|---|---|
| J6 | Main | 3V3, GND, SCL, SDA |
| J5 | Pulse-sensor board | SDA, SCL, GND, 3V3 |
| J7 | Main | SDA, SCL, GND, 3V3 |
| J8 | Temperature board | 3V3, GND, SCL, SDA |
| J1 | Main ("GPS MODULE") | 3V3, SEN_RX, SEN_TX, GND |

*Inferred:* J6 ↔ J5 and J7 ↔ J8 are cable pairs. Each pair has mirrored pin order, which suits a straight 4-wire JST cable between two boards that face each other.

## Power design

```
DC jack (J9) ──► SW1 ON/OFF ──► LM7805 (U6) ──► 5 V ──► DevKitC EXT_5V
                    C3 0.33 µF ┘          └ C4 0.1 µF
                                   DevKitC on-board 3.3 V LDO ──► +3.3 V rail ──► all sensors
                                                                 (C1 0.1 µF, C2 100 µF)
```

- The input voltage is not set in the design files. A 7805 normally needs about 7 V or more at the input for a stable 5 V output (general device rule, not stated in the project).
- The 3.3 V rail comes from the DevKitC's own regulator through its `3V3` pin. The carrier board adds bulk and decoupling capacitance only.
- The silkscreen marks a **"Heatsink Area"** next to the TO-220 regulator.
- The DevKitC can also be powered from its own USB port while you program it.

## PCB specifications

| Parameter | Value |
|---|---|
| EDA tool | KiCad 9.0 (Gerbers from Pcbnew 9.0.2) |
| Overall panel extent | 123.6 × 59.8 mm (from the Gerber job file) |
| Board outlines | 3 separate outlines: **main** 81.4 × 59.8 mm · **pulse-sensor board** 40.7 × 23.3 mm · **temperature board** 25.8 × 14.1 mm |
| Stack-up | 2 copper layers, FR4, 1.6 mm, 35 µm copper, no finish specified |
| Track width | 0.6 mm (all 119 segments) |
| Clearance | 0.5 mm |
| Vias | 7 vias, 1.4 mm pad / 0.6 mm drill |
| Copper pours | GND on B.Cu (one zone per board) |
| Keep-outs | Copper/track/via keep-out under the ESP32 antenna |
| Drill sizes | PTH 0.6 – 1.1 mm, NPTH 3.0 mm |
| Components | All on the top side, through-hole or plug-in modules |

### Fabrication variants

Both variants come from the same `.kicad_pcb` file and were exported on 2026-03-19.

| | `two_layer/` | `one_layer/` |
|---|---|---|
| Copper Gerbers | `F_Cu` + `B_Cu` | `B_Cu` only |
| Routing | 107 bottom + 12 top segments, 7 vias | Same bottom copper. The 12 top segments are absent |
| Other layers | Masks, paste, silk, Edge.Cuts, PTH/NPTH drill | Identical |
| Archive | `two_layer.zip` | `one_layer.zip` |
| Use case | Standard fab house order | Single-sided / home etching / low-cost prototype |

The top-copper traces carry only `MCU_TX`, `MCU_RX` and a short `GND` link. *Inferred:* when you build the single-layer version, these few links are made with wire jumpers through the via holes. The 1-layer job file still lists `LayerNumber: 2`, because it was exported from the 2-layer stack-up with only the F.Cu plot omitted.

## Gallery

| 3D top | 3D bottom |
|---|---|
|  |  |

**PCB layout**

**Schematic** ([PDF](docs/schematic.pdf))

## Repository structure

```
Cow-Health-Monitor/
├── README.md
├── docs/
│   ├── schematic.pdf
│   └── images/                  # 3D renders, layout & schematic SVGs
├── cow_pcb/
│   ├── cow_pcb.kicad_pro        # KiCad 9 project
│   ├── cow_pcb.kicad_sch        # Schematic
│   ├── cow_pcb.kicad_pcb        # PCB layout (3 board outlines)
│   ├── two_layer/  (+ .zip)     # 2-layer Gerbers + drill + job file
│   └── one_layer/  (+ .zip)     # 1-layer (B.Cu only) Gerbers + drill + job file
└── lib/
    ├── esp32 pinout.txt                        # DevKitC header map (layout notes)
    ├── IRThermoSensor/                         # GY-906 / HW-691 3D model (SolidWorks, STEP, Parasolid)
    ├── SEN0344_fermion-max30102-…_V2.0/        # DFRobot SEN0344 KiCad symbol/footprint, Altium lib, STEP
    ├── slide-switch-slw-116641-3a-ra-s-d-…/    # Slide switch STEP + preview images
    └── kicad-symbols/                          # Small legacy .lib symbols (GY-906, SSD1306, TP5591)
```

## How to open and manufacture

1. Install **KiCad 9.x** and open `cow_pcb/cow_pcb.kicad_pro`.
   - The schematic and PCB embed their symbols and footprints, so both open without extra libraries.
   - Some 3D models are linked by **absolute paths** (`D:/…`). Two of them, the ESP32-DevKitC and GY-87/GY-521 STEP files, are not in this repo. The 3D viewer will show those parts without bodies until you re-point the paths, for example to `${KIPRJMOD}/../lib/...`.
2. **Ordering boards:** upload `cow_pcb/two_layer.zip` (or `one_layer.zip`) to any PCB fab. The file has three separate outlines, so check whether your fab treats it as a multi-design panel. You can also separate the boards before ordering.
3. **Assembly:** all parts are through-hole or plug-in modules. Solder the regulator, capacitors, resistors, switch, jack and headers, then plug in the DevKitC and sensor modules.
4. Connect the remote sensor boards with 4-pin JST-XH cables (J6↔J5, J7↔J8). Fit the J3/J4 jumpers to link the GPS to UART0.

## Status and next steps

- [x] Schematic captured
- [x] PCB layout (main board + 2 sensor boards) routed
- [x] Gerbers exported in 1-layer and 2-layer variants
- [ ] Firmware (sensor drivers, data upload over Wi-Fi/BLE): not part of this repo
- [ ] Bench bring-up and validation
- Possible improvements: make the 3D-model paths project-relative, add I²C pull-ups on the carrier, connect the sensor `INT` lines to free GPIOs, add a power-input voltage rating and reverse-polarity protection, and consider a buck converter in place of the 7805 for battery operation.

---

**Author:** [@zeyad-hisham-cyper](https://github.com/zeyad-hisham-cyper) — Embedded Systems & PCB Design · Part of the [Freelance Projects](../README.md) portfolio

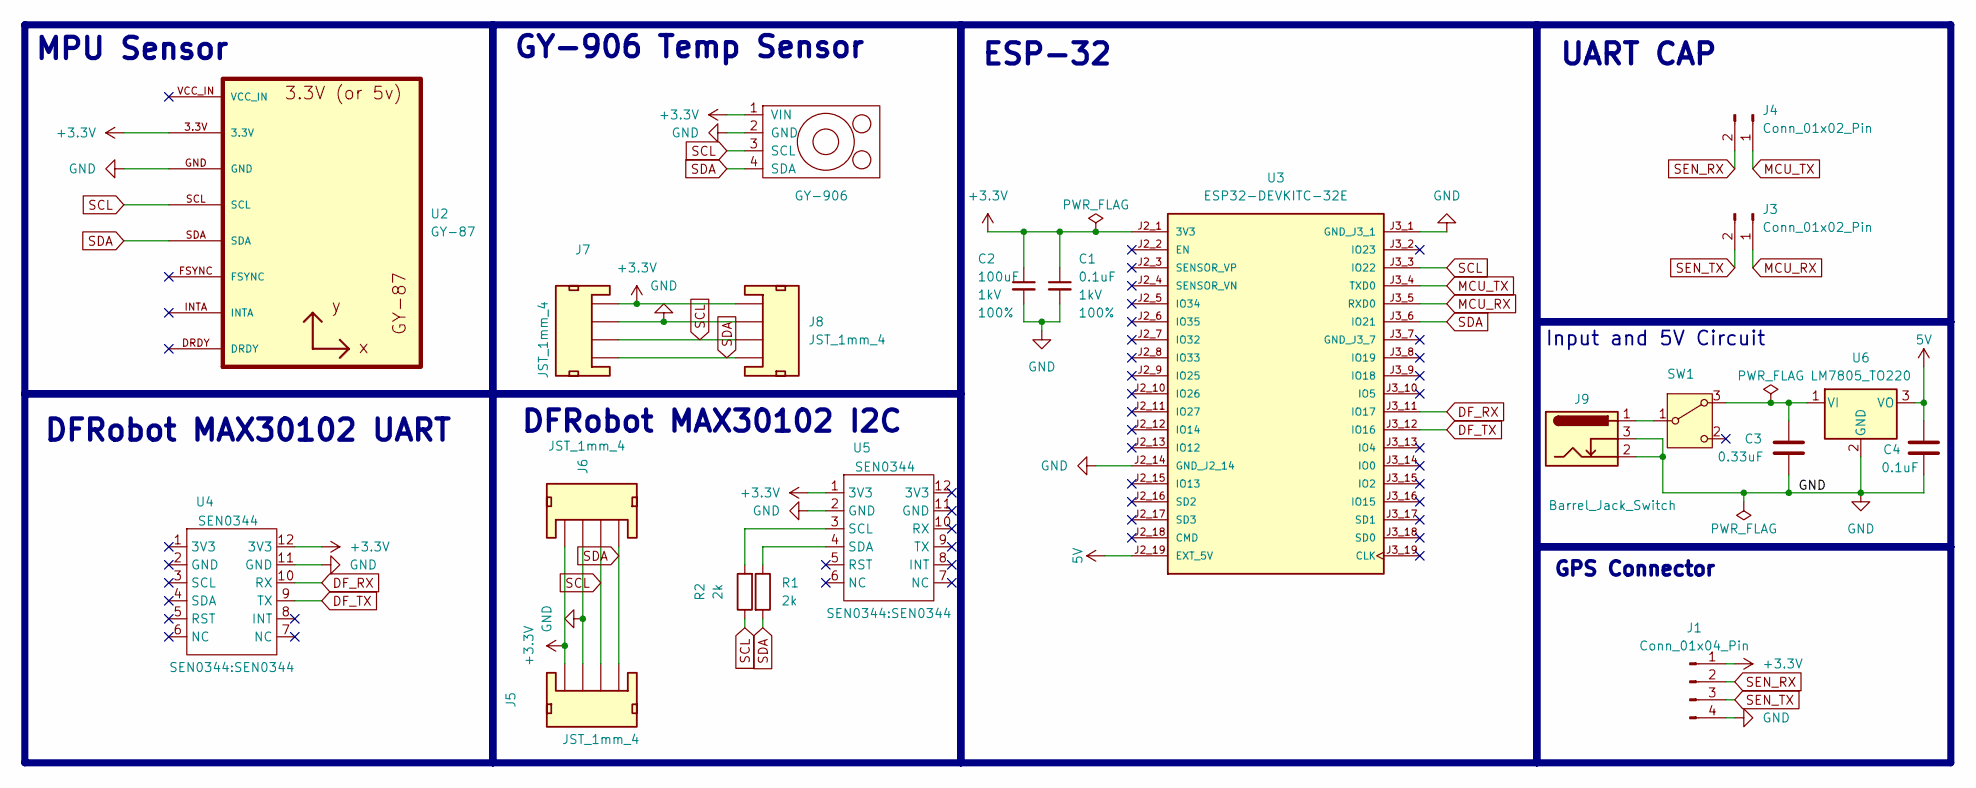
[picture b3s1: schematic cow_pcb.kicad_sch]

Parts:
C1: 0.1uF; C_Radial_D5.0mm_H5.0mm_P2.00mm; Voltage 1kV; Tolerance 100%
C2: 100uF; C_Radial_D5.0mm_H5.0mm_P2.00mm; Voltage 1kV; Tolerance 100%
C3: 0.33uF; C_Radial_D5.0mm_H5.0mm_P2.00mm
C4: 0.1uF; C_Radial_D5.0mm_H5.0mm_P2.00mm
J1: Conn_01x04_Pin; PinSocket_1x04_P2.54mm_Horizontal
J3, J4: Conn_01x02_Pin; PinHeader_1x02_P2.54mm_Vertical
J5, J6, J7, J8: JST_1mm_4; JST_XH_B4B-XH-A_1x04_P2.50mm_Vertical
J9: Barrel_Jack_Switch; BarrelJack_Horizontal
R1, R2: 2k; R_Axial_DIN0207_L6.3mm_D2.5mm_P7.62mm_Horizontal
SW1: SW_Wuerth_450301014042; SW_Slide-03_Wuerth-WS-SLTV_10x2.5x6.4_P2.54mm
U1: GY-906; Untitled
U2: GY-87
U3: ESP32-DEVKITC-32E; MODULE_ESP32-DEVKITC-32E; PARTREV 1.4
U4, U5: SEN0344
U6: LM7805_TO220; TO-220-3_Vertical

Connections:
5V: C4.1, U3.J2_19 (EXT_5V), U6.3 (VO)
+3.3V: C1.1, C2.1, J1.1, J5.4, J6.1, J7.4, J8.1, U1.1 (VIN), U2.3.3V, U3.J2_1 (3V3), U4.12 (3V3), U5.1 (3V3); also elsewhere on the board
DF_RX: U3.J3_11 (IO17), U4.10 (RX); also elsewhere on the board
DF_TX: U3.J3_12 (IO16), U4.9 (TX); also elsewhere on the board
GND: C1.2, C2.2, C3.2, C4.2, J1.4, J5.3, J6.2, J7.3, J8.2, J9.2, J9.3, U1.2 (GND), U2.GND, U3.J2_14 (GND_J2_14), U3.J3_1 (GND_J3_1), U4.11 (GND), U5.2 (GND), U6.2 (GND); also elsewhere on the board
MCU_RX: J3.1, U3.J3_5 (RXD0)
MCU_TX: J4.1, U3.J3_4 (TXD0)
unnamed: C3.1, SW1.3 (A), U6.1 (VI)
unnamed: J9.1, SW1.1 (B)
unnamed 9: R2.2, U5.3 (SCL); also elsewhere on the board
unnamed 10: R1.1, U5.4 (SDA); also elsewhere on the board
SCL: J5.2, J6.3, J7.2, J8.3, R2.1, U1.3 (SCL), U2.SCL, U3.J3_3 (IO22)
SDA: J5.1, J6.4, J7.1, J8.4, R1.2, U1.4 (SDA), U2.SDA, U3.J3_6 (IO21)
SEN_RX: J1.2, J4.2
SEN_TX: J1.3, J3.2

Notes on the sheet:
DFRobot MAX30102 I2C
ESP-32
GPS Connector
UART CAP
GY-906 Temp Sensor
MPU Sensor
Input and 5V Circuit
DFRobot MAX30102 UART

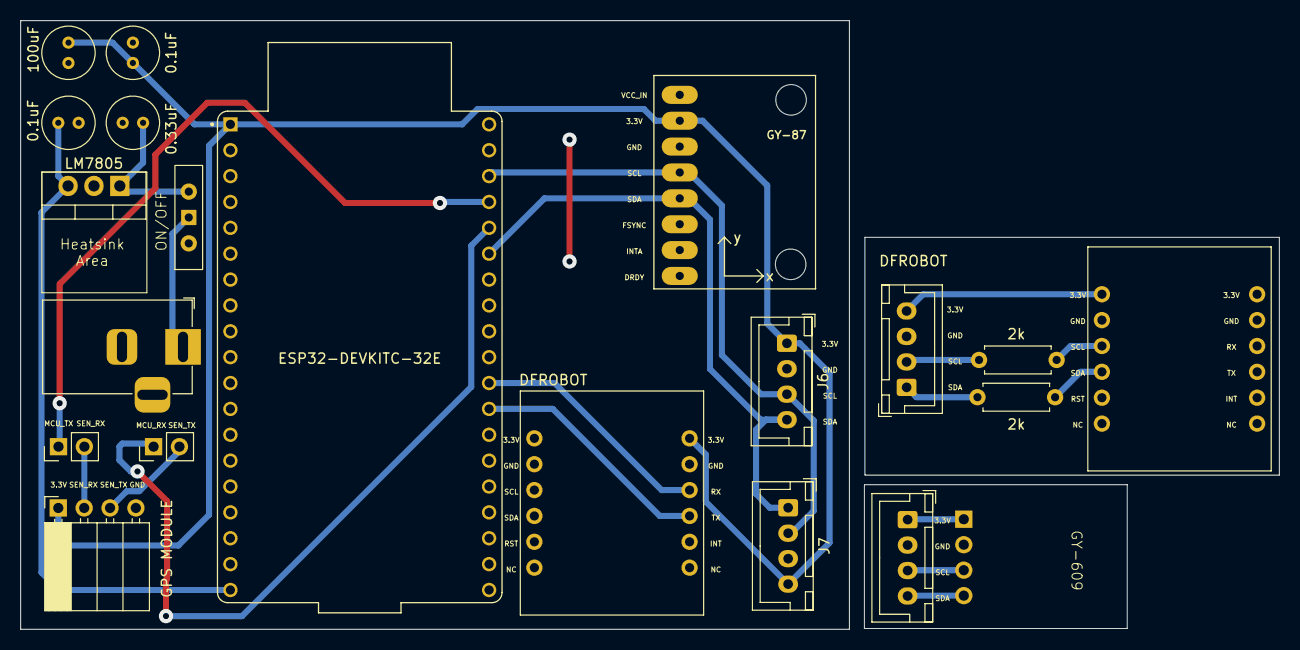
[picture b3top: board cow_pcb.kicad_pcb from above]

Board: 2 copper layers, 123.6 x 59.8 mm, 21 parts (0 on the bottom side), 15 nets.

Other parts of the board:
DFROBOT: SEN0344
DFROBOT#2: SEN0344

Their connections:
+3.3V: DFROBOT.12 (3V3), DFROBOT#2.1 (3V3); also elsewhere on the board
DF_RX: DFROBOT.10 (RX); also elsewhere on the board
DF_TX: DFROBOT.9 (TX); also elsewhere on the board
GND: DFROBOT.11 (GND), DFROBOT#2.2 (GND); also elsewhere on the board
unnamed 9: DFROBOT#2.3 (SCL); also elsewhere on the board
unnamed 10: DFROBOT#2.4 (SDA); also elsewhere on the board
